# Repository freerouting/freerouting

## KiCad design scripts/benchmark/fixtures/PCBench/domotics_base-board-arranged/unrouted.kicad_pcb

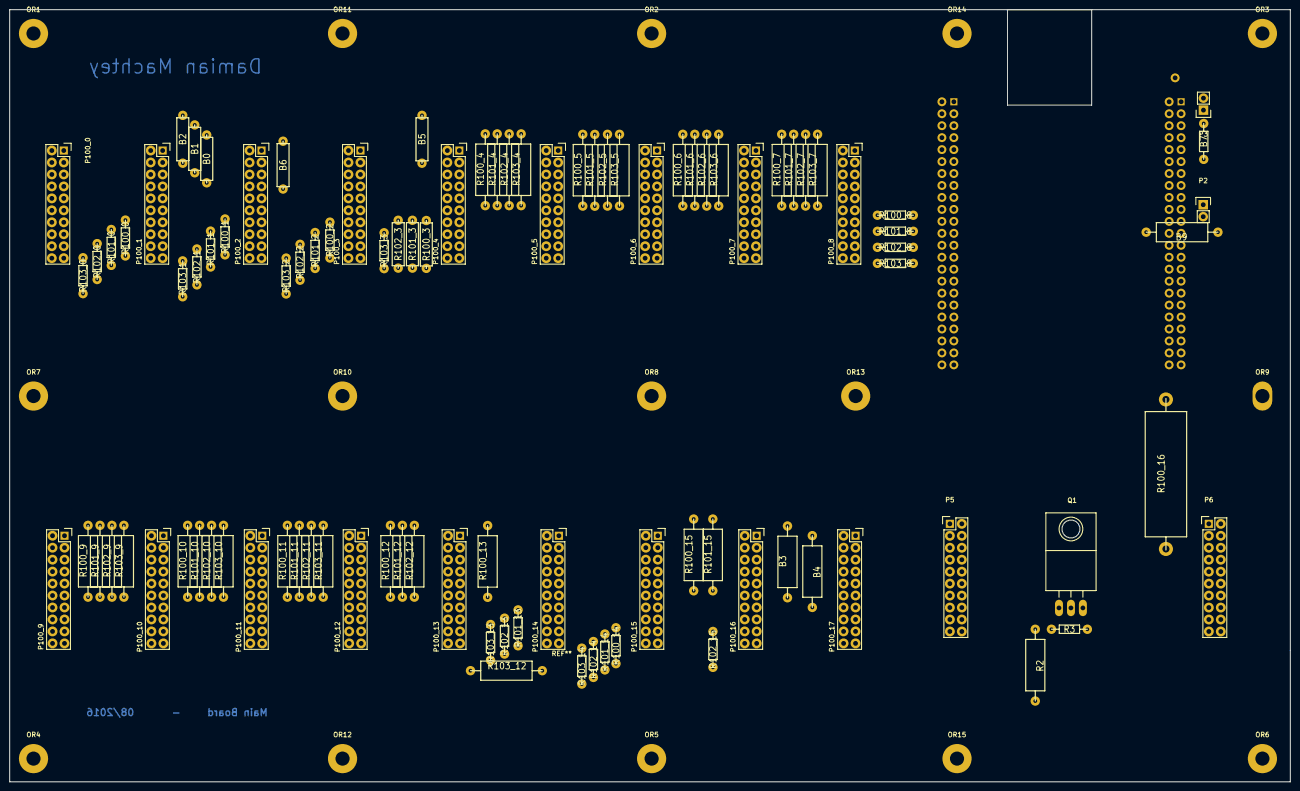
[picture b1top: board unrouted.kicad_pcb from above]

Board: 2 copper layers, 272.0 x 164.0 mm, 114 parts (0 on the bottom side), 191 nets, no tracks yet.

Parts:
B0, B1, B2, B5, B6: 0; RC05
B3, B4, B9: 0; RC07
B7: 0; RC03
OR1, OR2, OR3, OR4, OR5, OR6, OR7, OR8, OR9, OR10, OR11, OR12, OR13, OR14, OR15: Fix Hole; SolderWirePad_single_2-5mmDrill
P1: BEAGLEBONE_BLACK; BBB-reversed
P2: I2C; Pin_Header_Straight_1x02
P3: PWR; Pin_Header_Straight_1x02
P5, P6: CONN_02X10; Pin_Header_Straight_2x10
P100_0, P100_1, P100_2, P100_3, P100_4, P100_5, P100_6, P100_7, P100_8, P100_9, P100_10, P100_11, P100_12, P100_13, P100_14, P100_15, P100_16, P100_17: CONN_02X10; Socket_Strip_Straight_2x10
Q1: IRF540N; TO-220_Neutral123_Horizontal_LargePads
R2: 10k; RC07
R3: 47k; RC03
R100_0, R100_1, R100_2, R100_8, R100_14, R101_0, R101_1, R101_2, R101_8, R101_13, R101_14, R102_0, R102_1, R102_2, R102_8, R102_13, R102_14, R102_15, R103_0, R103_1, R103_2, R103_3, R103_8, R103_13, R103_14: 1K; RC03
R100_3, R101_3, R102_3: 1K; RC05
R100_4, R100_5, R100_6, R100_7, R100_9, R100_10, R100_11, R100_12, R100_13, R100_15, R101_4, R101_5, R101_6, R101_7, R101_9, R101_10, R101_11, R101_12, R101_15, R102_4, R102_5, R102_6, R102_7, R102_9, R102_10, R102_11, R102_12, R103_4, R103_5, R103_6, R103_7, R103_9, R103_10, R103_11, R103_12: 1K; RC07
R100_16: 1K; R25x8

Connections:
/12V+: B0.2, P5.7, P5.8, P100_9.7, P100_9.8, P100_10.7, P100_10.8, P100_11.7, P100_11.8, P100_12.7, P100_12.8, P100_13.7, P100_13.8, P100_14.7, P100_14.8, P100_15.7, P100_15.8, P100_16.7, P100_16.8, P100_17.7, P100_17.8
/12V+_TOP: B0.1, P100_0.7, P100_0.8, P100_1.7, P100_1.8, P100_2.7, P100_2.8, P100_3.7, P100_3.8, P100_4.7, P100_4.8, P100_5.7, P100_5.8, P100_6.7, P100_6.8, P100_7.7, P100_7.8, P100_8.7, P100_8.8
/AGND: P1.B34, P100_16.13, P100_16.14, P100_17.13, P100_17.14
/AIN0: P1.B39, P100_16.15, P100_16.16
/AIN1: P1.B40, P100_17.19, P100_17.20
/AIN2: P1.B37, P100_16.17, P100_16.18
/AIN3: P1.B38, P100_17.17, P100_17.18
/AIN4: P1.B33, P100_16.20
/AIN5: P1.B36, P100_17.15, P100_17.16
/AIN6: P1.B35, P100_16.19
/DC_3.3V: B2.2, P5.3, P5.4, P100_9.3, P100_9.4, P100_10.3, P100_10.4, P100_11.3, P100_11.4, P100_12.3, P100_12.4, P100_13.3, P100_13.4, P100_14.3, P100_14.4, P100_15.3, P100_15.4, P100_16.3, P100_16.4, P100_17.3, P100_17.4
/DC_3.3V_TOP: B2.1, B5.1, P100_0.3, P100_0.4, P100_1.3, P100_1.4, P100_2.3, P100_2.4, P100_3.3, P100_3.4, P100_4.3, P100_4.4, P100_5.3, P100_5.4, P100_6.3, P100_6.4, P100_7.3, P100_7.4, P100_8.3, P100_8.4
/DC_3.3Ve: B5.2, P1.B3, P1.B4
/GND: B4.1, P100_0.1, P100_0.2, P100_1.1, P100_1.2, P100_2.1, P100_2.2, P100_3.1, P100_3.2, P100_4.1, P100_4.2, P100_5.1, P100_5.2, P100_6.1, P100_6.2, P100_7.1, P100_7.2, P100_8.1, P100_8.2, P100_9.1, P100_9.2, P100_10.1, P100_10.2, P100_11.1, P100_11.2, P100_12.1, P100_12.2, P100_13.1, P100_13.2, P100_14.1, P100_14.2, P100_15.1, P100_15.2, P100_16.1, P100_16.2, P100_17.1, P100_17.2
/GND1: P1.B1, P1.B2, P3.2, P6.1, P6.2
/GND2: P1.A1, P1.A2
/GND3: P1.B43, P1.B44, P1.B45, P1.B46, Q1.3, R3.1
/GND12V: B1.2, P5.5, P5.6, P100_9.5, P100_9.6, P100_10.5, P100_10.6, P100_11.5, P100_11.6, P100_12.5, P100_12.6, P100_13.5, P100_13.6, P100_14.5, P100_14.6, P100_15.5, P100_15.6, P100_16.5, P100_16.6, P100_17.5, P100_17.6
/GND12V_TOP: B1.1, P100_0.5, P100_0.6, P100_1.5, P100_1.6, P100_2.5, P100_2.6, P100_3.5, P100_3.6, P100_4.5, P100_4.6, P100_5.5, P100_5.6, P100_6.5, P100_6.6, P100_7.5, P100_7.6, P100_8.5, P100_8.6
/GPIO0_2: P1.B22, R100_12.2
/GPIO0_3: P1.B21, R102_14.2
/GPIO0_4: P1.B18, R103_11.2
/GPIO0_5: P1.B17, R103_14.2
/GPIO0_7: P1.B42, R100_16.2
/GPIO0_8: P1.A35, R101_0.2
/GPIO0_9: P1.A33, R102_0.2
/GPIO0_10: P1.A31, R103_0.2
/GPIO0_11: P1.A32, R100_3.2
/GPIO0_14: P1.B26, R102_12.2
/GPIO0_15: P1.B24, R101_12.2
/GPIO0_20: B3.1, P1.B41
/GPIO0_22: P1.A19, R101_10.2
/GPIO0_23: P1.A13, R100_4.2
/GPIO0_26: P1.A14, R103_6.2
/GPIO0_27: P1.A17, R102_10.2
/GPIO0_30: P1.B11, R103_13.2
/GPIO0_31: P1.B13, R102_13.2
/GPIO1_0: P1.A25, R102_9.2
/GPIO1_1: P1.A24, R100_8.2
/GPIO1_2: P1.A5, R100_5.2
/GPIO1_3: P1.A6, R103_5.2
/GPIO1_4: P1.A23, R103_9.2
/GPIO1_5: P1.A22, R103_7.2
/GPIO1_6: P1.A3, R101_5.2
/GPIO1_7: P1.A4, R102_5.2
/GPIO1_12: P1.A12, R102_6.2
/GPIO1_13: P1.A11, R101_4.2
/GPIO1_14: P1.A16, R100_7.2
/GPIO1_15: P1.A15, R103_10.2
/GPIO1_16: P1.B15, R101_13.2
/GPIO1_17: P1.B23, R101_14.2
/GPIO1_18: P1.B14, R101_11.2
/GPIO1_19: P1.B16, R102_11.2
/GPIO1_28: P1.B12, R100_11.2
/GPIO1_29: P1.A26, R101_8.2
/GPIO1_30: P1.A21, R100_10.2
/GPIO1_31: P1.A20, R102_7.2
/GPIO2_1: P1.A18, R101_7.2
/GPIO2_2: P1.A7, R103_4.2
/GPIO2_3: P1.A8, R100_6.2
/GPIO2_4: P1.A10, R101_6.2
/GPIO2_5: P1.A9, R102_4.2
/GPIO2_6: P1.A45, R100_1.2
/GPIO2_7: P1.A46, R103_2.2
/GPIO2_8: P1.A43, R101_1.2
/GPIO2_9: P1.A44, R102_2.2
/GPIO2_10: P1.A41, R102_1.2
/GPIO2_11: P1.A42, R101_2.2
/GPIO2_12: P1.A39, R103_1.2
/GPIO2_13: P1.A40, R100_2.2
/GPIO2_14: P1.A37, R100_0.2
/GPIO2_15: P1.A38, R103_3.2
/GPIO2_16: P1.A36, R102_3.2
/GPIO2_17: P1.A34, R101_3.2
/GPIO2_22: P1.A27, R101_9.2
/GPIO2_23: P1.A29, R100_9.2
/GPIO2_24: P1.A28, R102_8.2
/GPIO2_25: P1.A30, R103_8.2
/GPIO3_14: P1.B31, R102_15.2
/GPIO3_15: P1.B29, R2.2
/GPIO3_16: P1.B30, R101_15.2
/GPIO3_17: P1.B28, R100_15.2
/GPIO3_19: P1.B27, R103_12.2
/GPIO3_21: P1.B25, R100_14.2
/I2C2_SCL: P1.B19, P2.2
/I2C2_SDA: B9.2, P1.B20
/PWR_BUT: B7.2, P1.B9
/SYS_5V: P1.B7, P1.B8
/VADC: P1.B32, P100_16.11, P100_16.12, P100_17.11, P100_17.12
/VDD_5V: P1.B5, P1.B6, P6.9, P6.10
/VDD_5V_DOWN: B6.2, P5.9, P5.10, P100_9.9, P100_9.10, P100_10.9, P100_10.10, P100_11.9, P100_11.10, P100_12.9, P100_12.10, P100_13.9, P100_13.10, P100_14.9, P100_14.10, P100_15.9, P100_15.10, P100_16.9, P100_16.10, P100_17.9, P100_17.10
/VDD_5V_TOP: B6.1, P100_0.9, P100_0.10, P100_1.9, P100_1.10, P100_2.9, P100_2.10, P100_3.9, P100_3.10, P100_4.9, P100_4.10, P100_5.9, P100_5.10, P100_6.9, P100_6.10, P100_7.9, P100_7.10, P100_8.9, P100_8.10
unnamed: B3.2, R100_13.2
unnamed: B4.2, Q1.2
unnamed: B7.1, P3.1
unnamed: B9.1, P2.1
unnamed: P5.1, P5.2
unnamed: P5.11, P5.12
unnamed: P5.13, P5.14
unnamed: P5.15, P5.16
unnamed: P5.17, P5.18
unnamed: P5.19, P5.20
unnamed: P6.3, P6.4
unnamed: P6.5, P6.6
unnamed: P6.7, P6.8
unnamed: P6.11, P6.12
unnamed: P6.13, P6.14
unnamed: P6.15, P6.16
unnamed: P6.17, P6.18
unnamed: P6.19, P6.20, R100_16.1
unnamed: P100_0.11, P100_0.12
unnamed: P100_0.13, P100_0.14, R100_0.1
unnamed: P100_0.15, P100_0.16, R101_0.1
unnamed: P100_0.17, P100_0.18, R102_0.1
unnamed: P100_0.19, P100_0.20, R103_0.1
unnamed: P100_1.11, P100_1.12
unnamed: P100_1.13, P100_1.14, R100_1.1
unnamed: P100_1.15, P100_1.16, R101_1.1
unnamed: P100_1.17, P100_1.18, R102_1.1
unnamed: P100_1.19, P100_1.20, R103_1.1
unnamed: P100_2.11, P100_2.12
unnamed: P100_2.13, P100_2.14, R100_2.1
unnamed: P100_2.15, P100_2.16, R101_2.1
unnamed: P100_2.17, P100_2.18, R102_2.1
unnamed: P100_2.19, P100_2.20, R103_2.1
unnamed: P100_3.11, P100_3.12
unnamed: P100_3.13, P100_3.14, R100_3.1
unnamed: P100_3.15, P100_3.16, R101_3.1
unnamed: P100_3.17, P100_3.18, R102_3.1
unnamed: P100_3.19, P100_3.20, R103_3.1
unnamed: P100_4.11, P100_4.12
unnamed: P100_4.13, P100_4.14, R100_4.1
unnamed: P100_4.15, P100_4.16, R101_4.1
unnamed: P100_4.17, P100_4.18, R102_4.1
unnamed: P100_4.19, P100_4.20, R103_4.1
unnamed: P100_5.11, P100_5.12
unnamed: P100_5.13, P100_5.14, R100_5.1
unnamed: P100_5.15, P100_5.16, R101_5.1
unnamed: P100_5.17, P100_5.18, R102_5.1
unnamed: P100_5.19, P100_5.20, R103_5.1
unnamed: P100_6.11, P100_6.12
unnamed: P100_6.13, P100_6.14, R100_6.1
unnamed: P100_6.15, P100_6.16, R101_6.1
unnamed: P100_6.17, P100_6.18, R102_6.1
unnamed: P100_6.19, P100_6.20, R103_6.1
unnamed: P100_7.11, P100_7.12
unnamed: P100_7.13, P100_7.14, R100_7.1
unnamed: P100_7.15, P100_7.16, R101_7.1
unnamed: P100_7.17, P100_7.18, R102_7.1
unnamed: P100_7.19, P100_7.20, R103_7.1
unnamed: P100_8.11, P100_8.12
unnamed: P100_8.13, P100_8.14, R100_8.1
unnamed: P100_8.15, P100_8.16, R101_8.1
unnamed: P100_8.17, P100_8.18, R102_8.1
unnamed: P100_8.19, P100_8.20, R103_8.1
unnamed: P100_9.11, P100_9.12
unnamed: P100_9.13, P100_9.14, R100_9.1
unnamed: P100_9.15, P100_9.16, R101_9.1
unnamed: P100_9.17, P100_9.18, R102_9.1
unnamed: P100_9.19, P100_9.20, R103_9.1
unnamed: P100_10.11, P100_10.12
unnamed: P100_10.13, P100_10.14, R100_10.1
unnamed: P100_10.15, P100_10.16, R101_10.1
unnamed: P100_10.17, P100_10.18, R102_10.1
unnamed: P100_10.19, P100_10.20, R103_10.1
unnamed: P100_11.11, P100_11.12
unnamed: P100_11.13, P100_11.14, R100_11.1
unnamed: P100_11.15, P100_11.16, R101_11.1
unnamed: P100_11.17, P100_11.18, R102_11.1
unnamed: P100_11.19, P100_11.20, R103_11.1
unnamed: P100_12.11, P100_12.12
unnamed: P100_12.13, P100_12.14, R100_12.1
unnamed: P100_12.15, P100_12.16, R101_12.1
unnamed: P100_12.17, P100_12.18, R102_12.1
unnamed: P100_12.19, P100_12.20, R103_12.1
unnamed: P100_13.11, P100_13.12
unnamed: P100_13.13, P100_13.14, R100_13.1
unnamed: P100_13.15, P100_13.16, R101_13.1
unnamed: P100_13.17, P100_13.18, R102_13.1
unnamed: P100_13.19, P100_13.20, R103_13.1
unnamed: P100_14.11, P100_14.12
unnamed: P100_14.13, P100_14.14, R100_14.1
unnamed: P100_14.15, P100_14.16, R101_14.1
unnamed: P100_14.17, P100_14.18, R102_14.1
unnamed: P100_14.19, P100_14.20, R103_14.1
unnamed: P100_15.11, P100_15.12
unnamed: P100_15.13, P100_15.14, R100_15.1
unnamed: P100_15.15, P100_15.16, R101_15.1
unnamed: P100_15.17, P100_15.18, R102_15.1
unnamed: P100_15.19, P100_15.20
unnamed: Q1.1, R2.1, R3.2

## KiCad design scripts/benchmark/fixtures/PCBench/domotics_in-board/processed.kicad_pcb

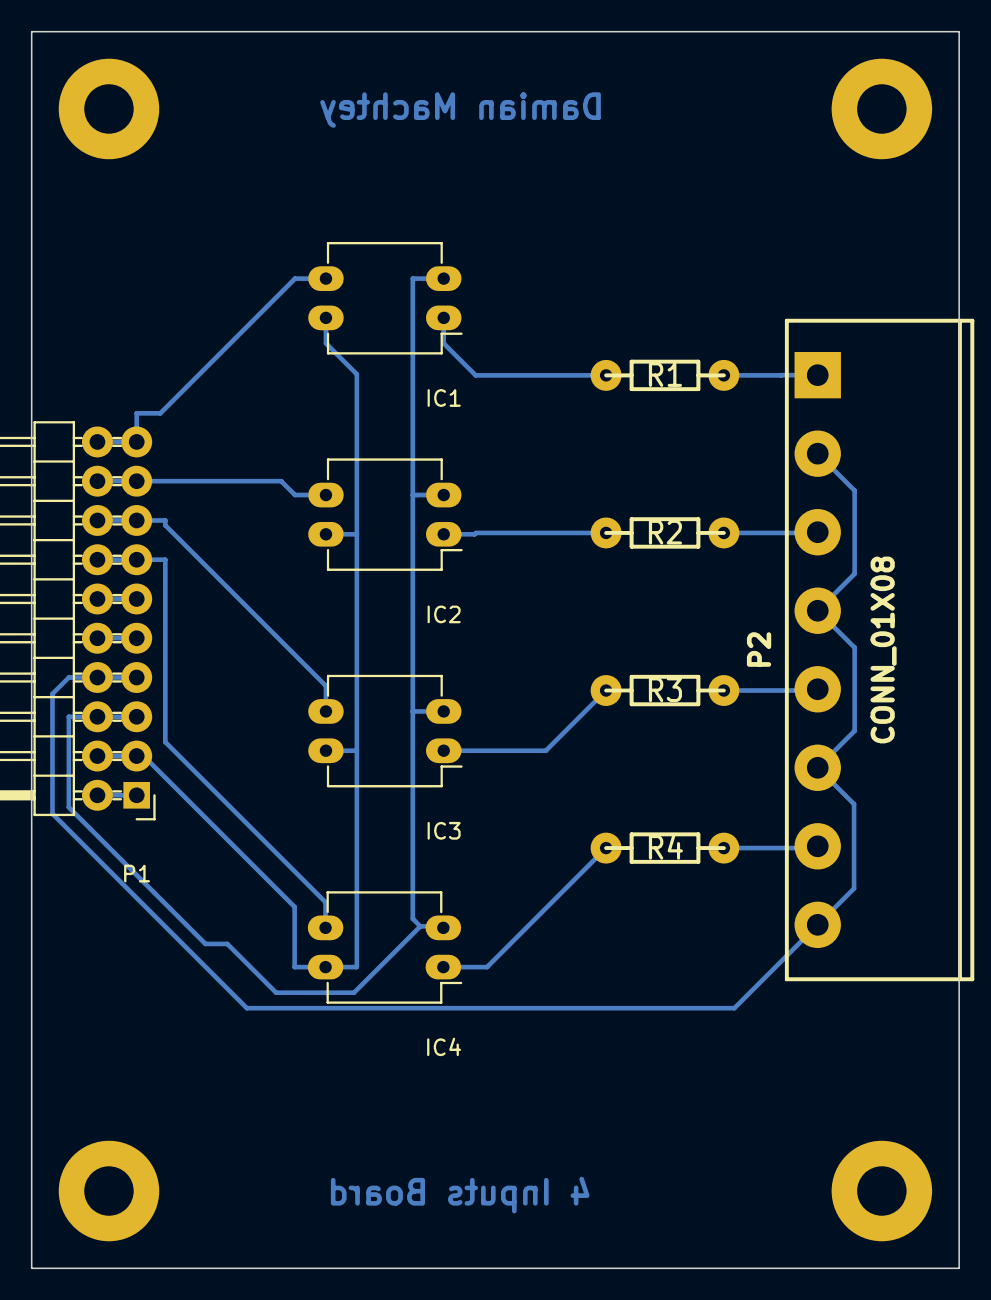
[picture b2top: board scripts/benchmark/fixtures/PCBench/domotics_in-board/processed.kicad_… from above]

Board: 2 copper layers, 60.0 x 80.0 mm, 14 parts (0 on the bottom side), 18 nets.

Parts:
IC1, IC2, IC3, IC4: PC817; DIP-4_W7.62mm_LongPads
OR1, OR2, OR3, OR4: SolderWirePad_single_2-5mmDrill
P1: CONN_02X10; Pin_Header_Angled_2x10
P2: CONN_01X08; mstba_2,5%2f8-g-5,08
R1, R2, R3, R4: 1.5k; RC03

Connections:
/3.3V: IC1.4, IC2.4, IC3.4, IC4.4, P1.3, P1.4
/+12VDC: P1.7, P1.8, P2.2, P2.4, P2.6, P2.8
/GND: P1.1, P1.2
/GND12V: IC1.2, IC2.2, IC3.2, IC4.2, P1.5, P1.6
/gpio_1: IC1.3, P1.19, P1.20
/gpio_2: IC2.3, P1.17, P1.18
/gpio_3: IC3.3, P1.15, P1.16
/gpio_4: IC4.3, P1.13, P1.14
/in_1: P2.1, R1.1
/in_2: P2.3, R2.1
/in_3: P2.5, R3.1
/in_4: P2.7, R4.1
unnamed: IC1.1, R1.2
unnamed: IC2.1, R2.2
unnamed: IC3.1, R3.2
unnamed: IC4.1, R4.2
unnamed: P1.9, P1.10
unnamed: P1.11, P1.12

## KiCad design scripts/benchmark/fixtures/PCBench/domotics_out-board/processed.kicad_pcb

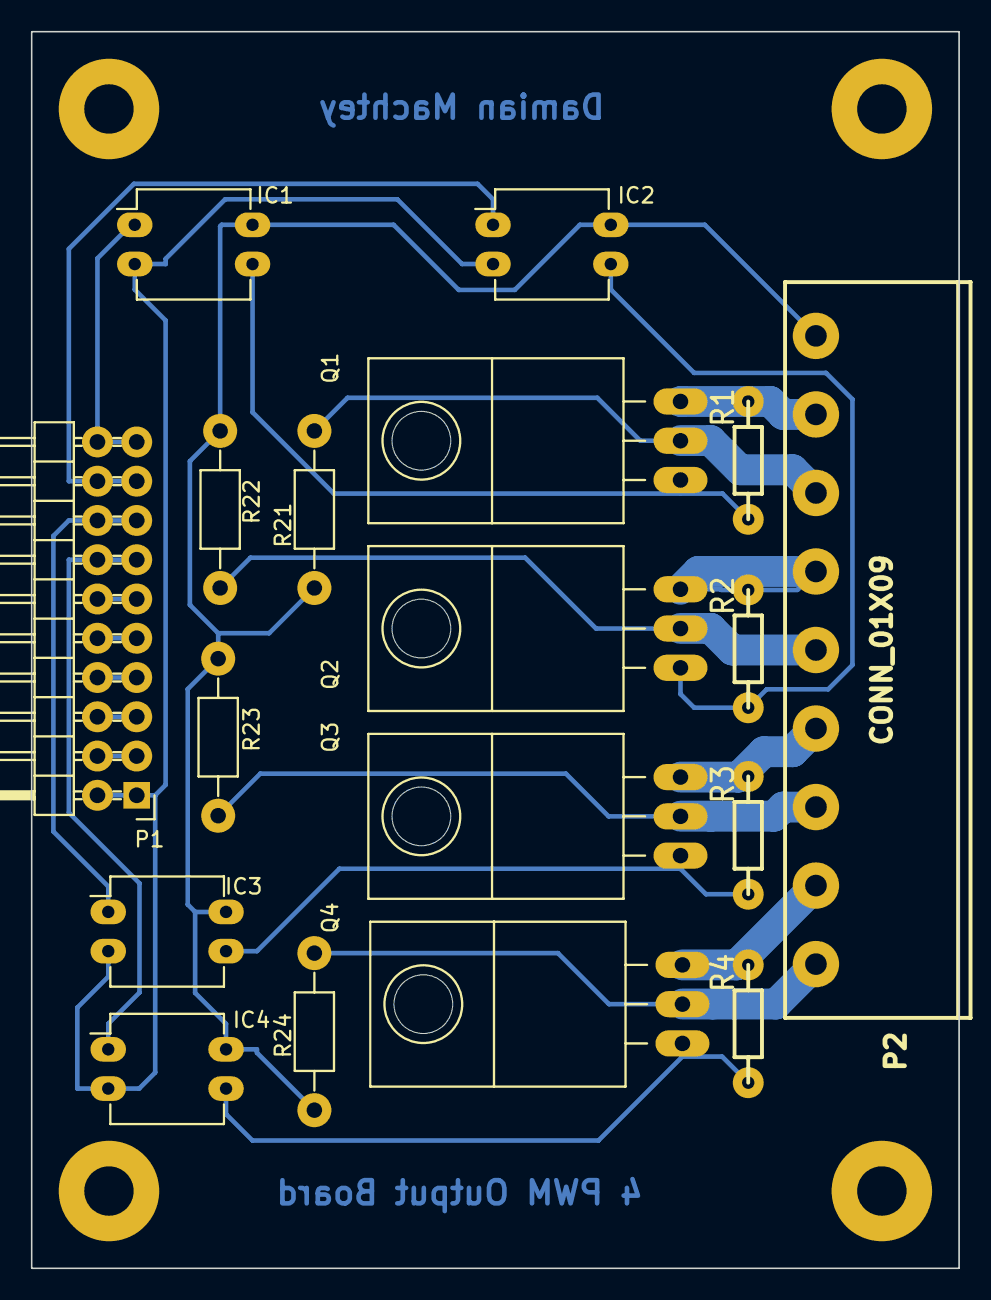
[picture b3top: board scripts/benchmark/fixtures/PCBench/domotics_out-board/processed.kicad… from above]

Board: 2 copper layers, 60.0 x 80.0 mm, 22 parts (0 on the bottom side), 23 nets.

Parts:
IC1, IC2, IC3, IC4: PC817; DIP-4_W7.62mm_LongPads
OR1, OR2, OR3, OR4: SolderWirePad_single_2-5mmDrill
P1: CONN_02X10; Pin_Header_Angled_2x10
P2: CONN_01X09; mstba_2,5%2f9-g-5,08
Q1, Q2, Q3, Q4: IRF540N; TO-220_Neutral123_Horizontal_LargePads
R1: 4K7; RC03
R2, R3, R4: 4k7; RC03
R21, R22, R23, R24: 100k; Resistor_H_RM10mm

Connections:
/3.3V: P1.3, P1.4
/+12V: IC1.4, IC2.4, IC3.4, IC4.4, P2.1, R21.1, R22.1, R23.1, R24.1
/+12VDC: P1.7, P1.8
/-12V_1: P2.2, Q1.3, R1.2
/-12V_2: P2.4, Q2.3, R2.2
/-12V_3: P2.6, Q3.3, R3.2
/-12V_4: P2.8, Q4.3, R4.2
/GND: IC1.2, IC2.2, IC3.2, IC4.2, P1.1, P1.2
/GND12V: P1.5, P1.6
/OUT_1: P2.3, Q1.2, R21.2
/OUT_2: P2.5, Q2.2, R22.2
/OUT_3: P2.7, Q3.2, R23.2
/OUT_4: P2.9, Q4.2, R24.2
/in_1: IC1.1, P1.19, P1.20
/in_2: IC2.1, P1.17, P1.18
/in_3: IC3.1, P1.15, P1.16
/in_4: IC4.1, P1.13, P1.14
unnamed: IC1.3, Q1.1, R1.1
unnamed: IC2.3, Q2.1, R2.1
unnamed: IC3.3, Q3.1, R3.1
unnamed: IC4.3, Q4.1, R4.1
unnamed: P1.9, P1.10
unnamed: P1.11, P1.12

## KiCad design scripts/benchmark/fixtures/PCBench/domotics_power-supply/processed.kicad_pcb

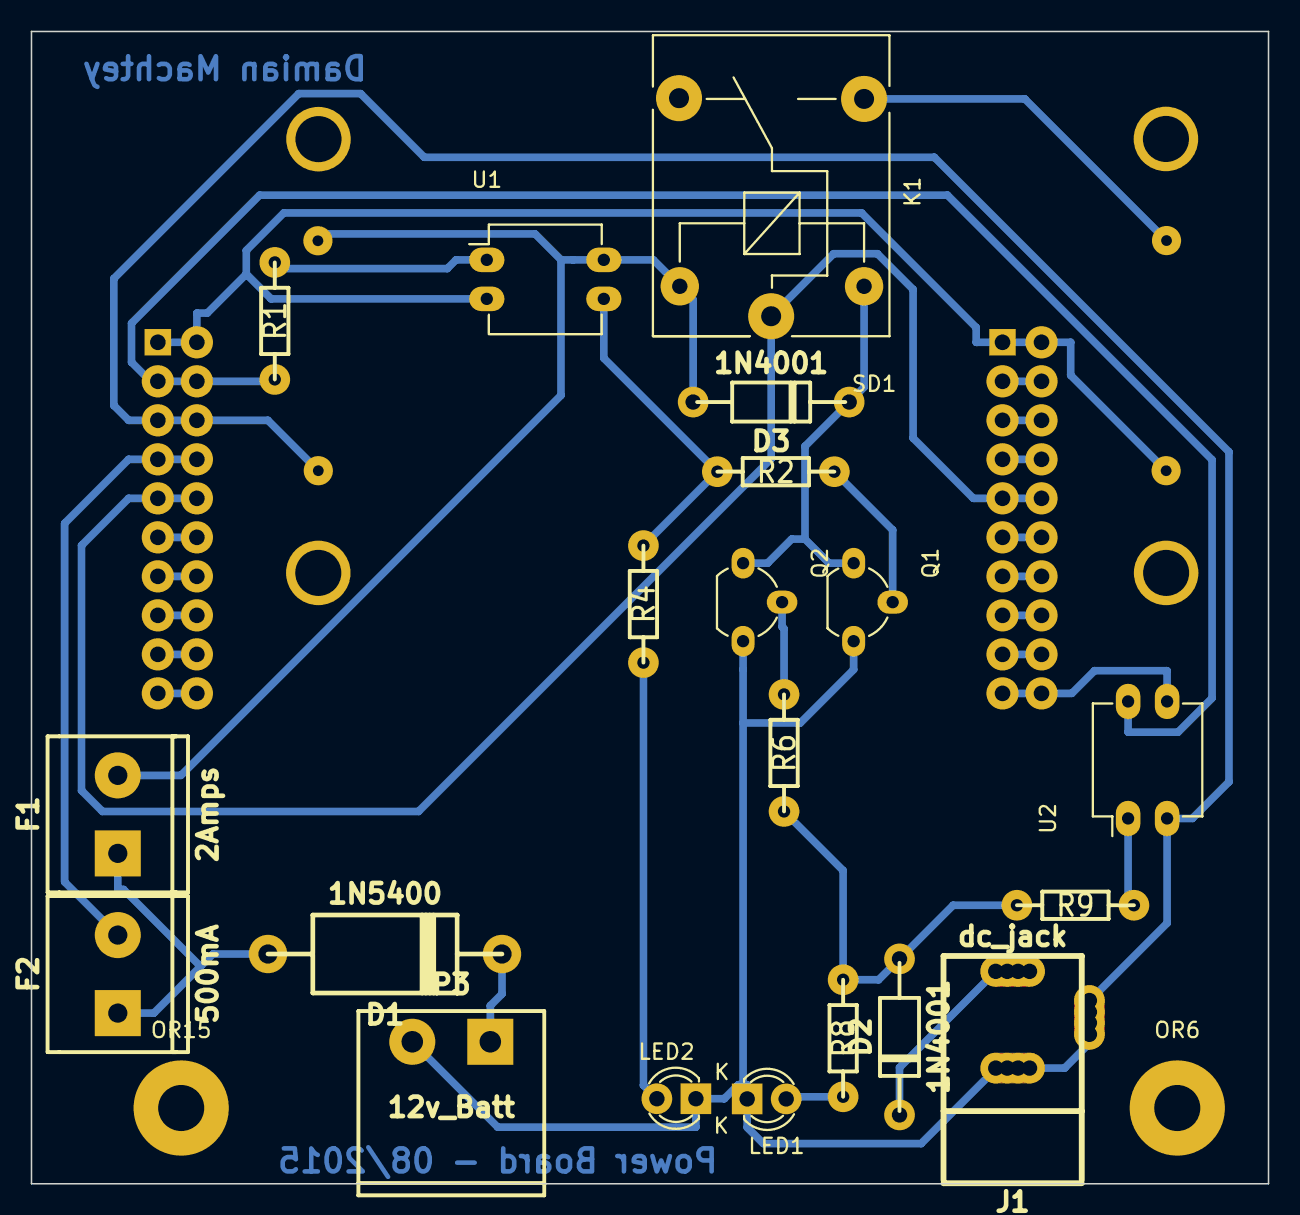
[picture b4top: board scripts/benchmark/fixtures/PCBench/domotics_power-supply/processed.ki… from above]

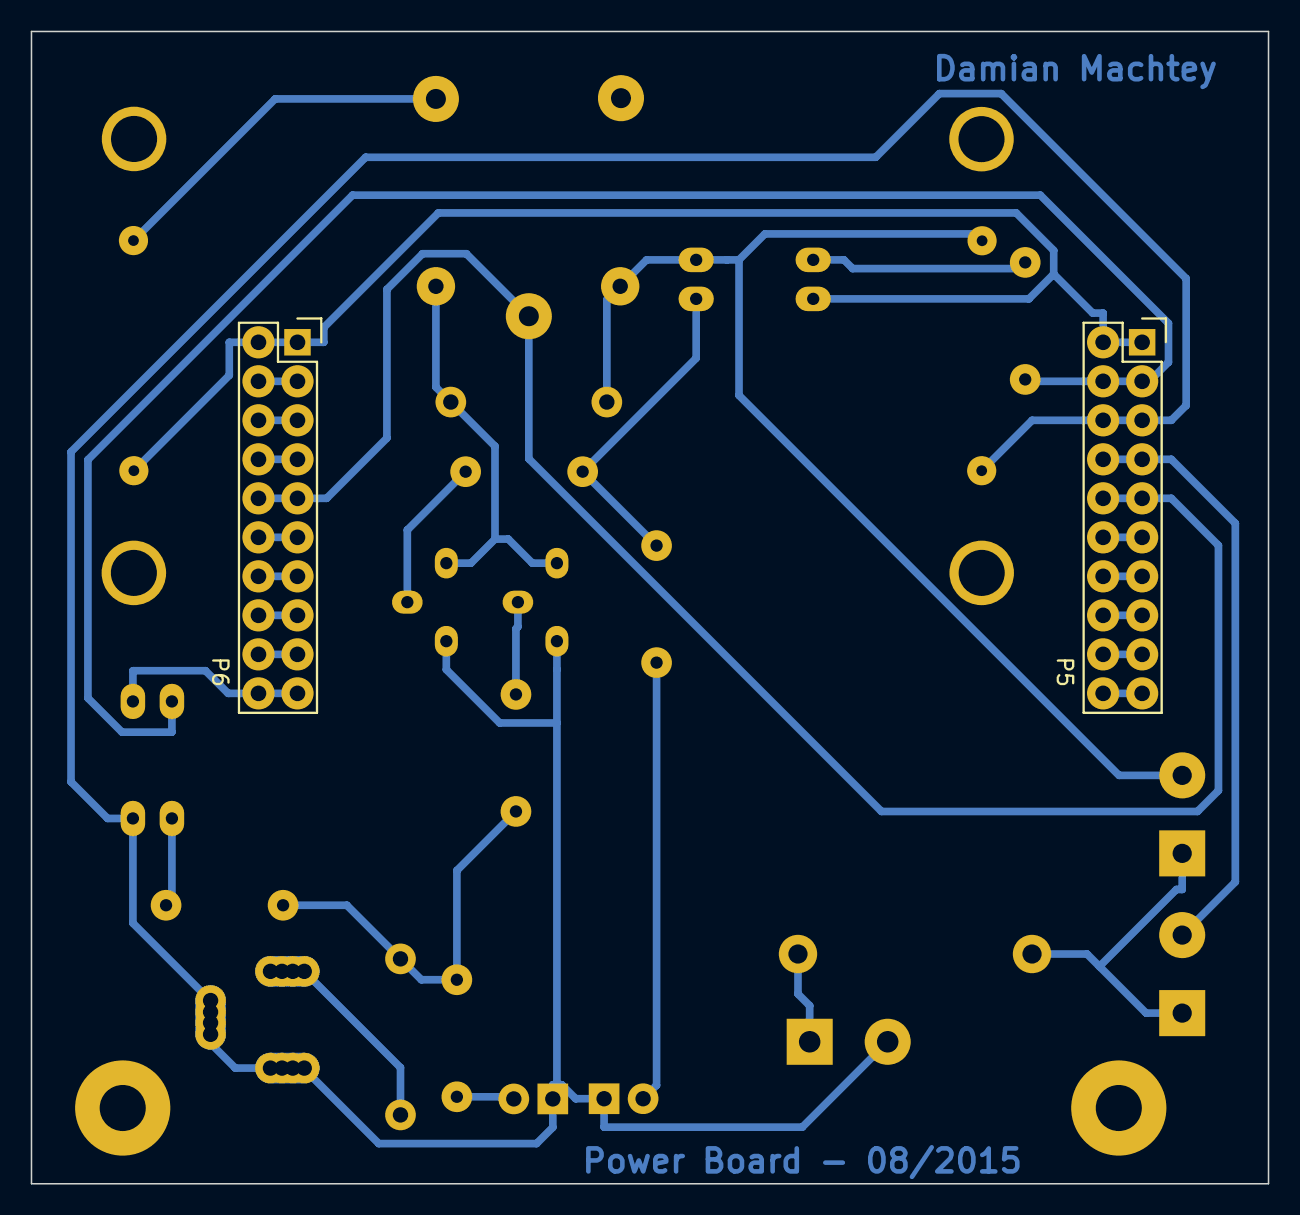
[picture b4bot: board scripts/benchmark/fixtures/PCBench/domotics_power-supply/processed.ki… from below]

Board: 2 copper layers, 80.5 x 75.0 mm, 25 parts (2 on the bottom side), 32 nets.

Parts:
D1: 1N5400; diode_do201
D2, D3: 1N4001; diode_do41
F1: 2Amps; mors_2p
F2: 500mA; mors_2p
J1: dc_jack; dc_socket_rh
K1: 5v Supply; Relay_SANYOU_SRD_Series_Form_C
LED1: Mains; LED-3MM
LED2: BBB; LED-3MM
OR6, OR15: Fix Hole; SolderWirePad_single_2-5mmDrill
P3: 12v_Batt; mstba_2,5%2f2-g-5,08
P5, P6: CONN_02X10; Socket_Strip_Straight_2x10
Q1, Q2: BC547; TO-92_Molded_Wide_Oval
R1: 1K; RC03
R2, R4, R6, R8: 560; RC03
R9: 3k3; RC03
SD1: Step-Down-board; step-down
U1, U2: PC817; DIP-4_W7.62mm_LongPads

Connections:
/12V+: D3.1, F1.2, K1.5, SD1.1, U1.4
/12V+B: F2.2, P5.7, P5.8
/12V+Mains: D2.1, R6.2, R8.2, R9.1
/DC_3.3V: P5.3, P5.4, R1.2, U2.4
/GND: P5.1, P5.2, P6.1, P6.2, SD1.4, U1.2
/GND12V: J1.1, J1.2, LED1.1, LED2.1, P3.2, P5.5, P5.6, Q1.3, Q2.3, SD1.2, U2.2
/GPIO0_7: P6.19, P6.20, U2.3
/VDD_5V: K1.1, P5.9, P5.10, P6.9, P6.10
/VDD_5V-SD: K1.3, SD1.3
unnamed: D1.1, F1.1, F2.1
unnamed: D1.2, P3.1
unnamed: D2.2, J1.3
unnamed: D3.2, K1.2, Q1.1, Q2.1
unnamed: LED1.2, R8.1
unnamed: LED2.2, R4.2
unnamed: P5.11, P5.12
unnamed: P5.13, P5.14
unnamed: P5.15, P5.16
unnamed: P5.17, P5.18
unnamed: P5.19, P5.20
unnamed: P6.3, P6.4
unnamed: P6.5, P6.6
unnamed: P6.7, P6.8
unnamed: P6.11, P6.12
unnamed: P6.13, P6.14
unnamed: P6.15, P6.16
unnamed: P6.17, P6.18
unnamed: Q1.2, R2.2
unnamed: Q2.2, R6.1
unnamed: R1.1, U1.1
unnamed: R2.1, R4.1, U1.3
unnamed: R9.2, U2.1
